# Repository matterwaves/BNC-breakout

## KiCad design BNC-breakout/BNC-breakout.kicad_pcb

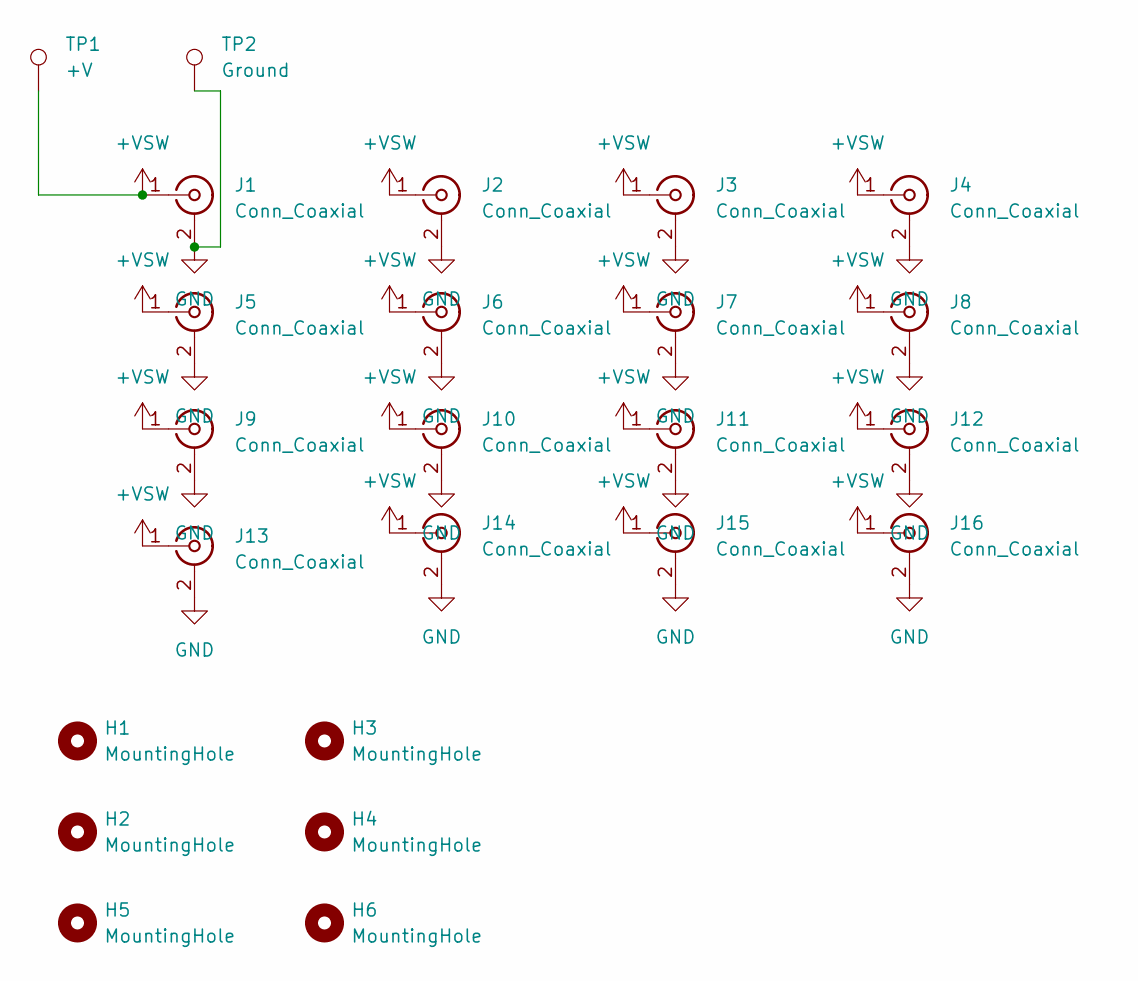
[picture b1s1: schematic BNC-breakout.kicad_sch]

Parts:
H1, H2, H3, H4, H5, H6: MountingHole; Mounting-Hole-Slot-6mm
J1, J2, J3, J4, J5, J6, J7, J8, J9, J10, J11, J12, J13, J14, J15, J16: Conn_Coaxial; 031532951RFX; LCSC number C5443992
TP1: +V; SolderWire-4sqmm_1x01_D3mm_OD6mm
TP2: Ground; SolderWire-4sqmm_1x01_D3mm_OD6mm

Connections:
+VSW: J1.1 (In), J2.1 (In), J3.1 (In), J4.1 (In), J5.1 (In), J6.1 (In), J7.1 (In), J8.1 (In), J9.1 (In), J10.1 (In), J11.1 (In), J12.1 (In), J13.1 (In), J14.1 (In), J15.1 (In), J16.1 (In), TP1.1; also elsewhere on the board
GND: J1.2 (Ext), J2.2 (Ext), J3.2 (Ext), J4.2 (Ext), J5.2 (Ext), J6.2 (Ext), J7.2 (Ext), J8.2 (Ext), J9.2 (Ext), J10.2 (Ext), J11.2 (Ext), J12.2 (Ext), J13.2 (Ext), J14.2 (Ext), J15.2 (Ext), J16.2 (Ext), TP2.1; also elsewhere on the board

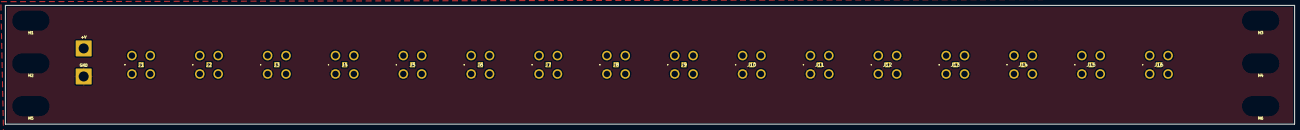
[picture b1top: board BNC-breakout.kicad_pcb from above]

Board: 4 copper layers, 482.6 x 44.4 mm, 24 parts (0 on the bottom side), 2 nets.

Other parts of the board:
+V: +V; SolderWire-4sqmm_1x01_D3mm_OD6mm
GND: Ground; SolderWire-4sqmm_1x01_D3mm_OD6mm

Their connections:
+VSW: +V.1; also elsewhere on the board
GND: GND.1; also elsewhere on the board

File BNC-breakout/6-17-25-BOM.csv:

Comment,Designator,Footprint,LCSC
BNC Connector,"J1,J2,J3,J4,J5,J6,J7,J8,J9,J10,J11,J12,J13,J14,J15,J16",SamacSys_Parts:031523951RFX,C5443992

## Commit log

2025-06-23 4-layer PCB. +V surrounded by GND
